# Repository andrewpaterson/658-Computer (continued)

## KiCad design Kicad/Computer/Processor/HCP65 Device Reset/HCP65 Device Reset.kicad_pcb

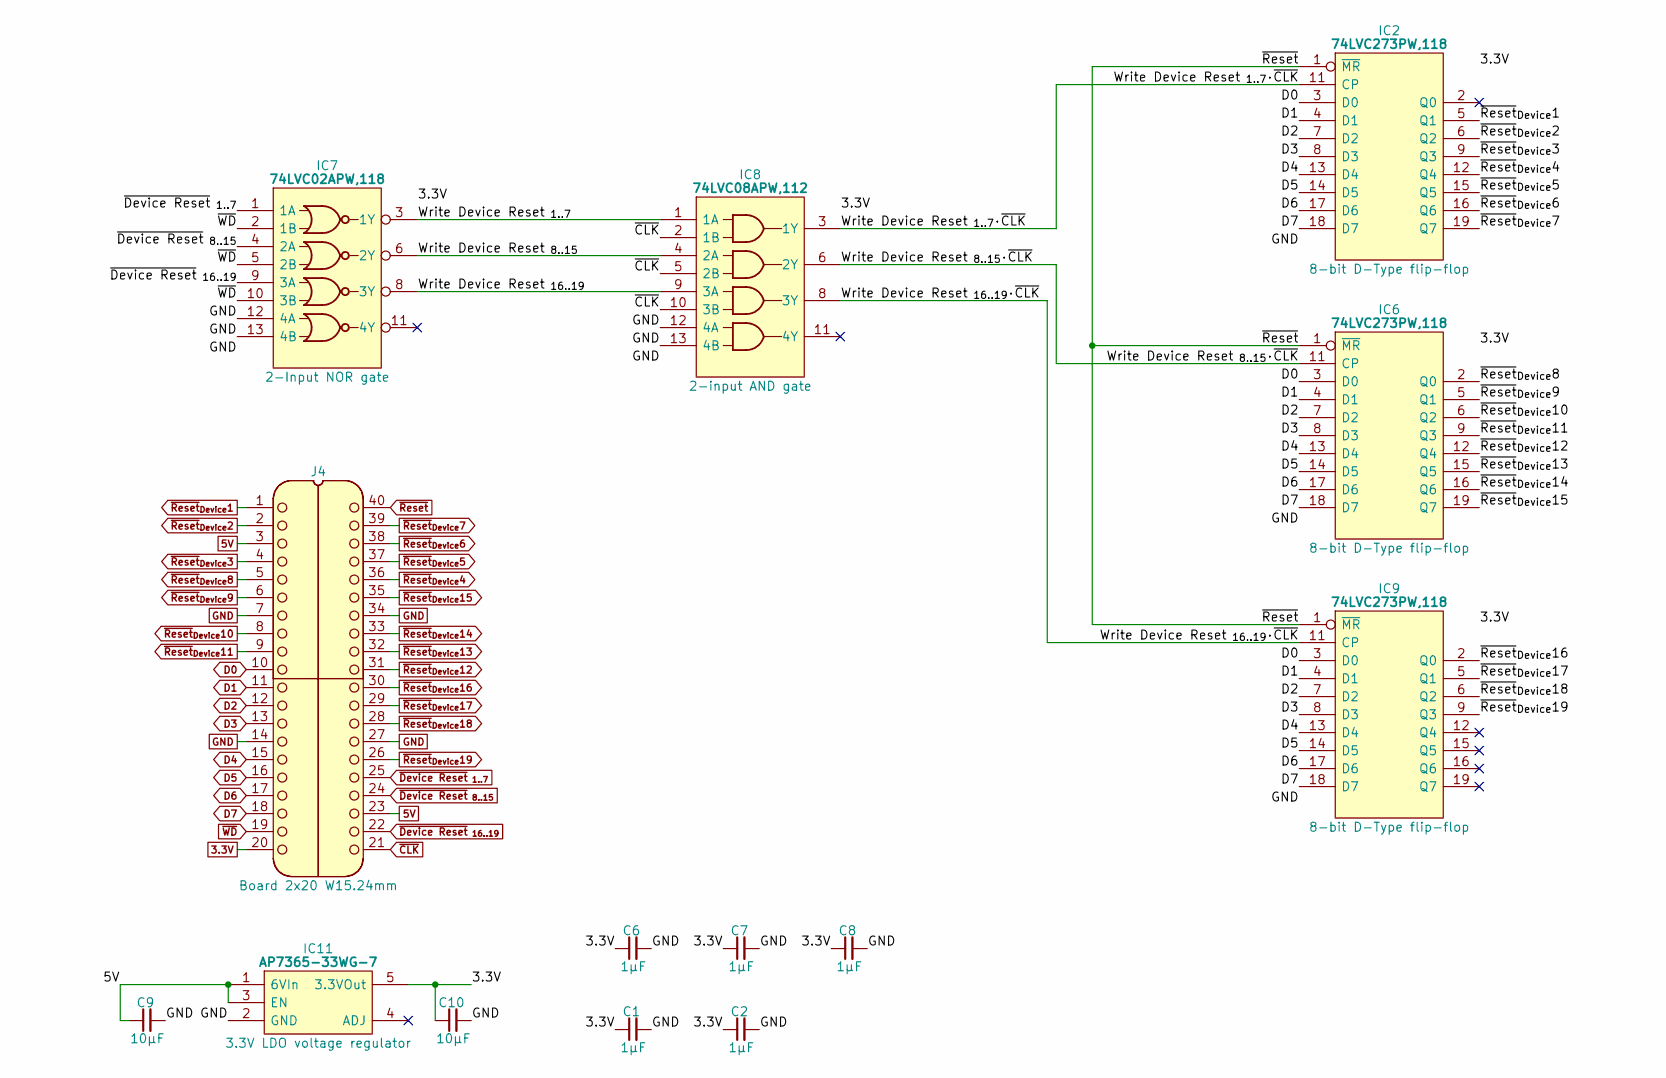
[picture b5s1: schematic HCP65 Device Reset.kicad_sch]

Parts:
C1, C2, C6, C7, C8: 1μF; C_0805
C9, C10: 10μF; C_0805
IC2, IC6, IC9: 74LVC273PW,118; SOP65P640X110-20N; Manufacturer_Part_Number 74LVC273PW,118; Mouser Part Number 771-74LVC273PW-T
IC7: 74LVC02APW,118; SOP65P640X110-14N; Mouser Part Number 771-74LVC02APW-T
IC8: 74LVC08APW,112; SOP65P640X110-14N; Manufacturer_Part_Number 74LVC08APW,112; Mouser Part Number 771-74LVC08APW
IC11: AP7365-33WG-7; SOT95P285X130-5N; Manufacturer_Part_Number AP7365-33WG-7; Mouser Part Number 621-AP7365-33WG-7
J4: Board 2x20 W15.24mm; DIP-40_Board_W15.24mm

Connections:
3.3V: C1.1, C2.1, C6.1, C7.1, C8.1, C10.1, IC2.20 (3V), IC6.20 (3V), IC7.14 (3V), IC8.14 (3V), IC9.20 (3V), IC11.5 (3.3VOut), J4.20
5V: C9.1, IC11.1 (6VIn), IC11.3 (EN), J4.3, J4.23
/Write Device Reset_{ 1..7}: IC7.3 (1Y), IC8.1 (1A)
/Write Device Reset_{ 1..7}·~CLK: IC2.11 (CP), IC8.3 (1Y)
/Write Device Reset_{ 8..15}: IC7.6 (2Y), IC8.4 (2A)
/Write Device Reset_{ 8..15}·~CLK: IC6.11 (CP), IC8.6 (2Y)
/Write Device Reset_{ 16..19}: IC7.8 (3Y), IC8.9 (3A)
/Write Device Reset_{ 16..19}·~CLK: IC8.8 (3Y), IC9.11 (CP)
D0: IC2.3 (D0), IC6.3 (D0), IC9.3 (D0), J4.10
D1: IC2.4 (D1), IC6.4 (D1), IC9.4 (D1), J4.11
D2: IC2.7 (D2), IC6.7 (D2), IC9.7 (D2), J4.12
D3: IC2.8 (D3), IC6.8 (D3), IC9.8 (D3), J4.13
D4: IC2.13 (D4), IC6.13 (D4), IC9.13 (D4), J4.15
D5: IC2.14 (D5), IC6.14 (D5), IC9.14 (D5), J4.16
D6: IC2.17 (D6), IC6.17 (D6), IC9.17 (D6), J4.17
D7: IC2.18 (D7), IC6.18 (D7), IC9.18 (D7), J4.18
GND: C1.2, C2.2, C6.2, C7.2, C8.2, C9.2, C10.2, IC2.10 (GND), IC6.10 (GND), IC7.7 (GND), IC7.12 (4A), IC7.13 (4B), IC8.7 (GND), IC8.12 (4A), IC8.13 (4B), IC9.10 (GND), IC11.2 (GND), J4.7, J4.14, J4.27, J4.34
~CLK: IC8.2 (1B), IC8.5 (2B), IC8.10 (3B), J4.21
~Device Reset_{ 1..7}: IC7.1 (1A), J4.25
~Device Reset_{ 8..15}: IC7.4 (2A), J4.24
~Device Reset_{ 16..19}: IC7.9 (3A), J4.22
~Reset: IC2.1 (~MR), IC6.1 (~MR), IC9.1 (~MR), J4.40
~Reset_{Device}1: IC2.5 (Q1), J4.1
~Reset_{Device}2: IC2.6 (Q2), J4.2
~Reset_{Device}3: IC2.9 (Q3), J4.4
~Reset_{Device}4: IC2.12 (Q4), J4.36
~Reset_{Device}5: IC2.15 (Q5), J4.37
~Reset_{Device}6: IC2.16 (Q6), J4.38
~Reset_{Device}7: IC2.19 (Q7), J4.39
~Reset_{Device}8: IC6.2 (Q0), J4.5
~Reset_{Device}9: IC6.5 (Q1), J4.6
~Reset_{Device}10: IC6.6 (Q2), J4.8
~Reset_{Device}11: IC6.9 (Q3), J4.9
~Reset_{Device}12: IC6.12 (Q4), J4.31
~Reset_{Device}13: IC6.15 (Q5), J4.32
~Reset_{Device}14: IC6.16 (Q6), J4.33
~Reset_{Device}15: IC6.19 (Q7), J4.35
~Reset_{Device}16: IC9.2 (Q0), J4.30
~Reset_{Device}17: IC9.5 (Q1), J4.29
~Reset_{Device}18: IC9.6 (Q2), J4.28
~Reset_{Device}19: IC9.9 (Q3), J4.26
~WD: IC7.2 (1B), IC7.5 (2B), IC7.10 (3B), J4.19

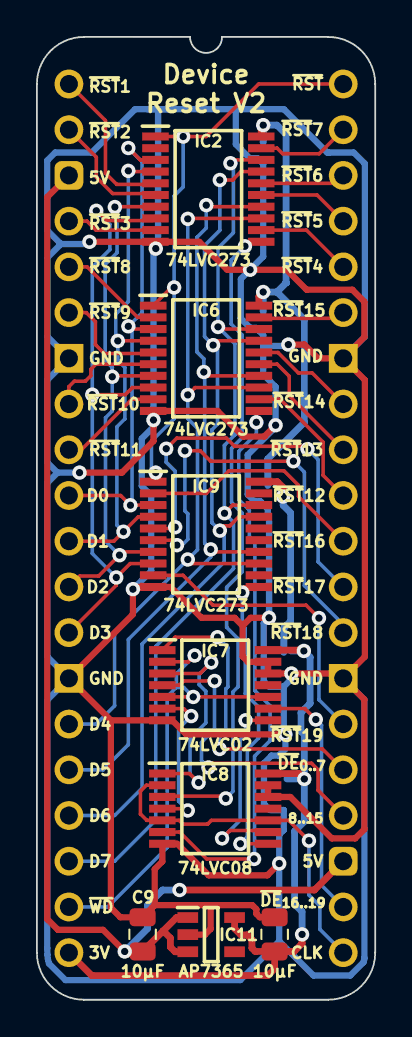
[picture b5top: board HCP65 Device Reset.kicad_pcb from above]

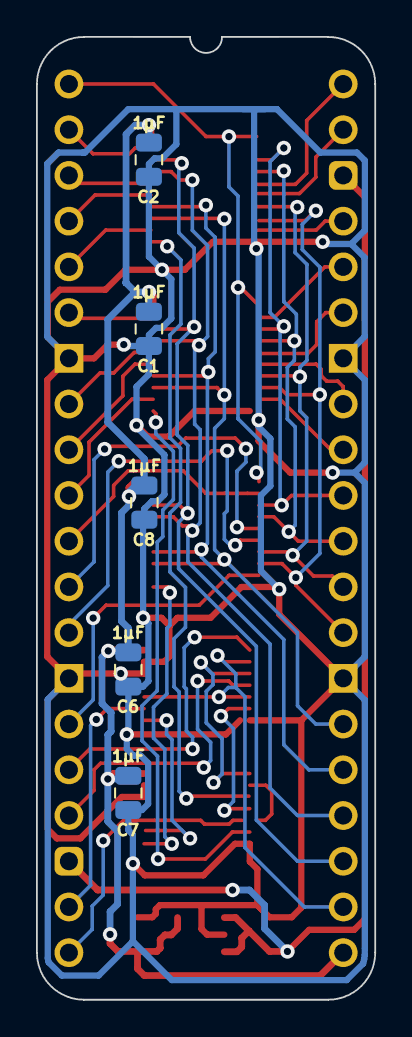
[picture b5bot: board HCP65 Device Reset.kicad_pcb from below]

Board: 2 copper layers, 18.8 x 53.5 mm, 14 parts (5 on the bottom side), 42 nets.

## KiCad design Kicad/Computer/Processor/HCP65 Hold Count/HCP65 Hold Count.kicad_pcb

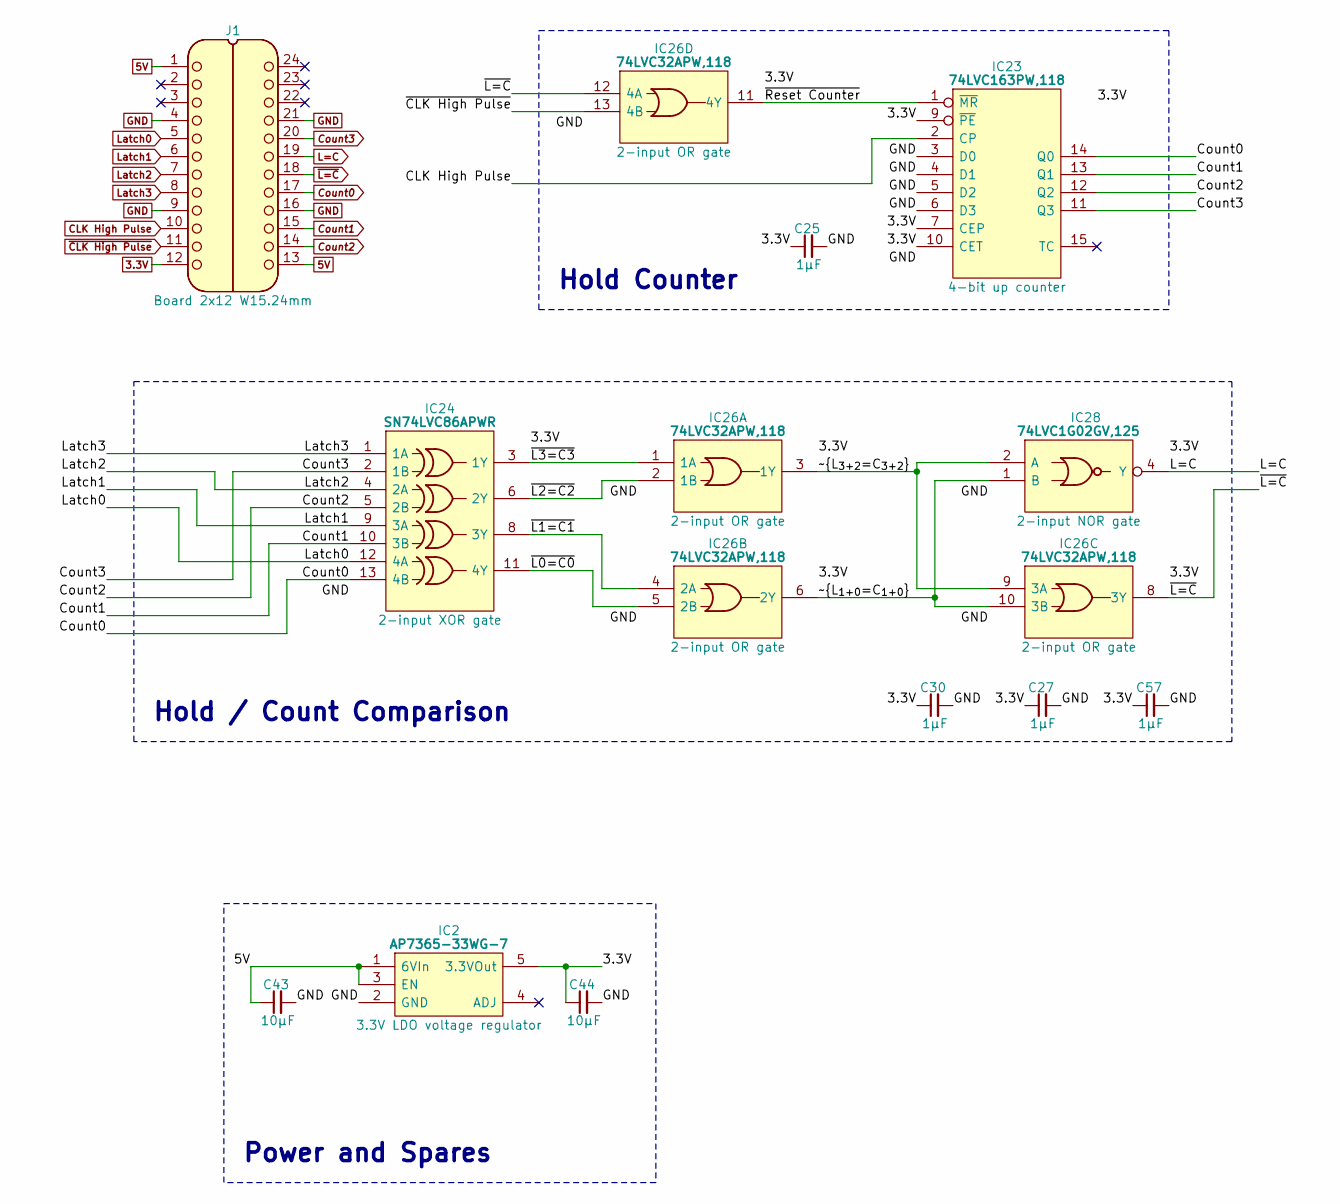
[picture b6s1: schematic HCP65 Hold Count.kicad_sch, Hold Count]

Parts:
C25, C27, C30, C57: 1μF; C_0805
C43, C44: 10μF; C_0805
IC2: AP7365-33WG-7; SOT95P285X130-5N; Manufacturer_Part_Number AP7365-33WG-7; Mouser Part Number 621-AP7365-33WG-7
IC23: 74LVC163PW,118; SOP65P640X110-16N; Mouser Part Number 771-74LVC163PW-T
IC24: SN74LVC86APWR; SOP65P640X120-14N; Manufacturer_Part_Number SN74LVC86APWR; Mouser Part Number 595-SN74LVC86APWR
IC26: 74LVC32APW,118; SOP65P640X110-14N; Manufacturer_Part_Number 74LVC32APW,118; Mouser Part Number 771-74LVC32APW-T
IC28: 74LVC1G02GV,125; SOT95P275X110-5N; Manufacturer_Part_Number 74LVC1G02GV,125; Mouser Part Number 771-LVC1G02GV125
J1: Board 2x12 W15.24mm; DIP-24_Board_W15.24mm

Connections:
3.3V: C25.1, C27.1, C30.1, C44.1, C57.1, IC2.5 (3.3VOut), IC23.7 (CEP), IC23.9 (~PE), IC23.10 (CET), IC23.16 (3V), IC24.14 (3V), IC26.14 (3V), IC28.5 (3V), J1.12
5V: C43.1, IC2.1 (6VIn), IC2.3 (EN), J1.1, J1.13
/~L0=C0: IC24.11 (4Y), IC26.5 (2B)
/~L1=C1: IC24.8 (3Y), IC26.4 (2A)
/~L2=C2: IC24.6 (2Y), IC26.2 (1B)
/~L3=C3: IC24.3 (1Y), IC26.1 (1A)
/~L_{1+0=C_{1+0}}: IC26.6 (2Y), IC26.10 (3B), IC28.1 (B)
/~L_{3+2=C_{3+2}}: IC26.3 (1Y), IC26.9 (3A), IC28.2 (A)
/~Reset Counter: IC23.1 (~MR), IC26.11 (4Y)
CLK High Pulse: IC23.2 (CP), J1.10
Count0: IC23.14 (Q0), IC24.13 (4B), J1.17
Count1: IC23.13 (Q1), IC24.10 (3B), J1.15
Count2: IC23.12 (Q2), IC24.5 (2B), J1.14
Count3: IC23.11 (Q3), IC24.2 (1B), J1.20
GND: C25.2, C27.2, C30.2, C43.2, C44.2, C57.2, IC2.2 (GND), IC23.3 (D0), IC23.4 (D1), IC23.5 (D2), IC23.6 (D3), IC23.8 (GND), IC24.7 (GND), IC26.7 (GND), IC28.3 (GND), J1.4, J1.9, J1.16, J1.21
L=C: IC28.4 (Y), J1.19
Latch0: IC24.12 (4A), J1.5
Latch1: IC24.9 (3A), J1.6
Latch2: IC24.4 (2A), J1.7
Latch3: IC24.1 (1A), J1.8
~CLK High Pulse: IC26.13 (4B), J1.11
~L=C: IC26.8 (3Y), IC26.12 (4A), J1.18

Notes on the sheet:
Power and Spares
Hold Counter
Hold / Count Comparison

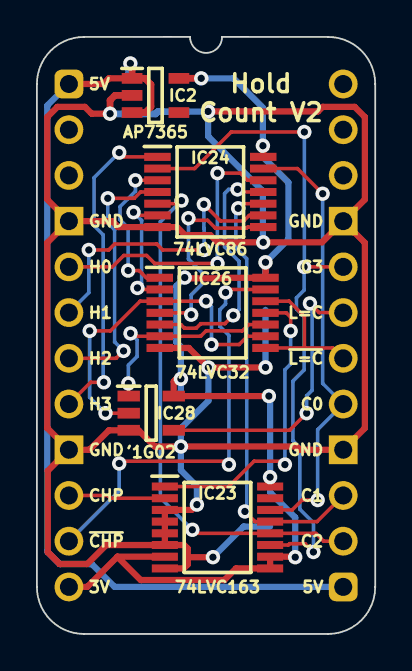
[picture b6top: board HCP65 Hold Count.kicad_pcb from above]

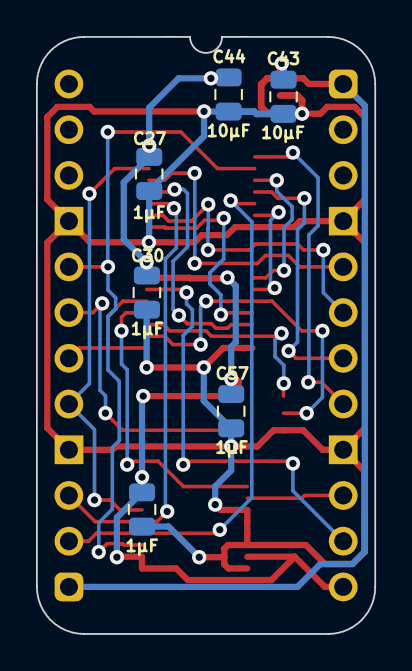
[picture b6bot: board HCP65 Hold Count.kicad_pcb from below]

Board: 2 copper layers, 18.8 x 33.2 mm, 12 parts (6 on the bottom side), 22 nets.

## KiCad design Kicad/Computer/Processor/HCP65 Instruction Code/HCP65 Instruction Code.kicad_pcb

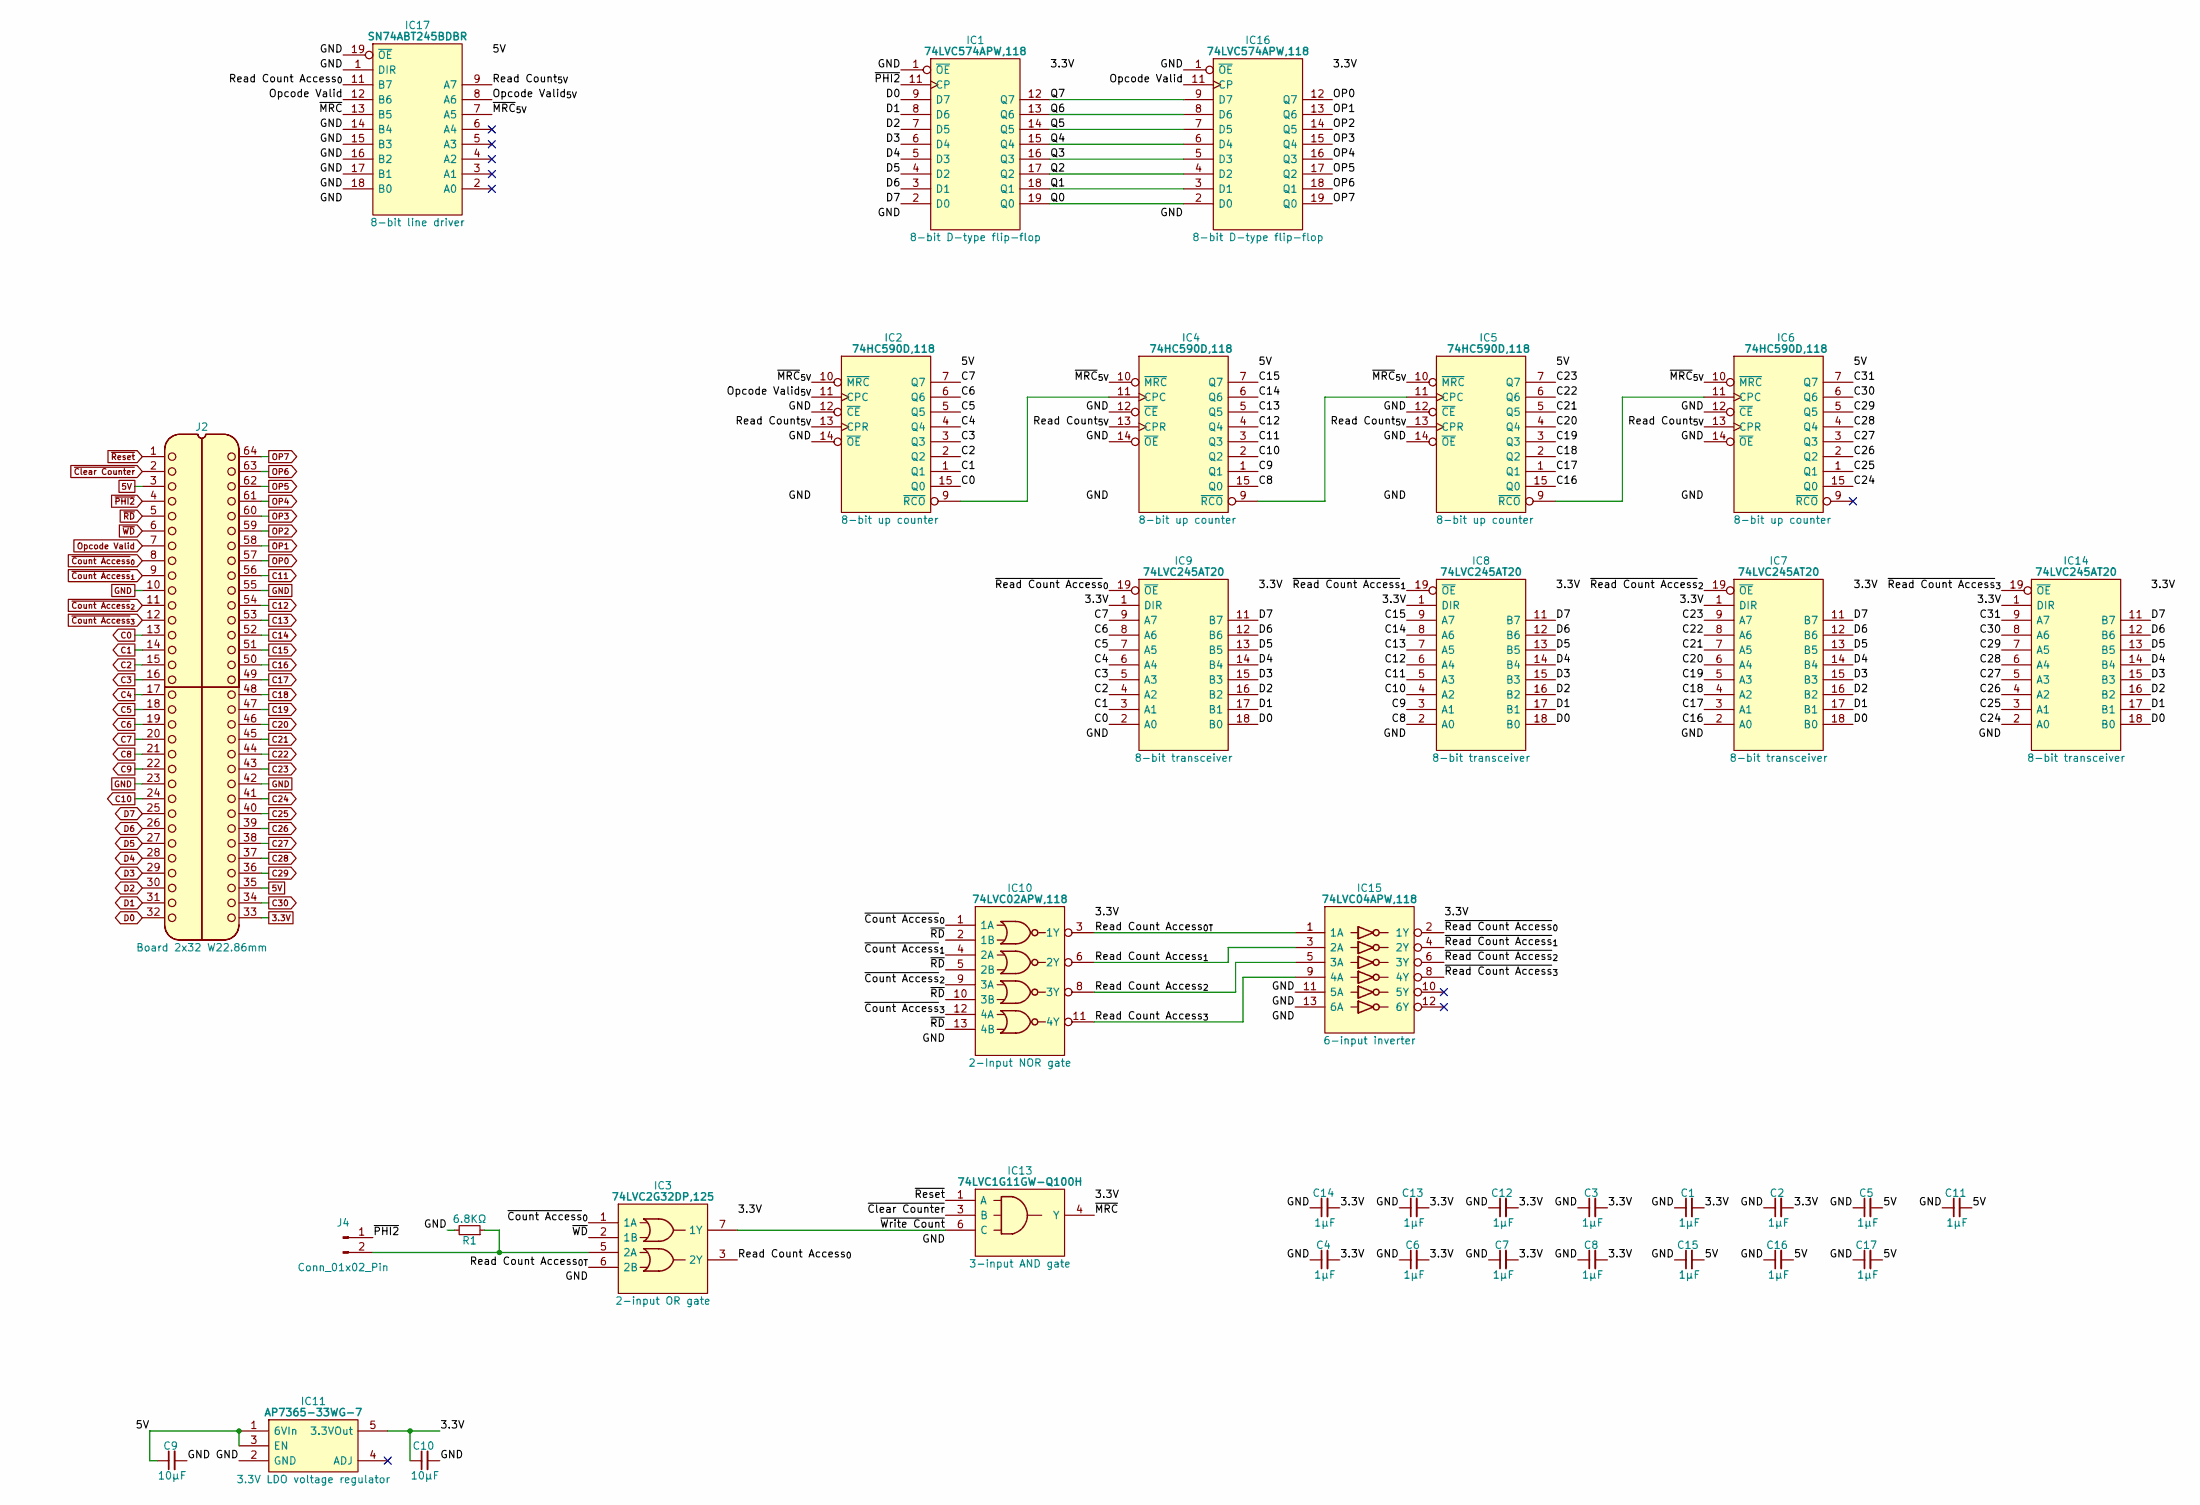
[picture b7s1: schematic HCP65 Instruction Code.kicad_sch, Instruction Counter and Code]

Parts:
C1, C2, C3, C4, C5, C6, C7, C8, C11, C12, C13, C14, C15, C16, C17: 1μF; C_0805
C9, C10: 10μF; C_0805
IC1, IC16: 74LVC574APW,118; SOP65P640X110-20N; Manufacturer_Part_Number 74LVC574APW,118; Mouser Part Number 771-74LVC574APW-T
IC2, IC4, IC5, IC6: 74HC590D,118; SOIC127P600X175-16N; Mouser Part Number 771-HC590D118
IC3: 74LVC2G32DP,125; SOP65P400X110-8N; Manufacturer_Part_Number 74LVC2G32DP,125; Mouser Part Number 771-LVC2G32DP125
IC7, IC8, IC9, IC14: 74LVC245AT20; SOP65P640X120-20N; Manufacturer_Part_Number 74LVC245AT20-13; Mouser Part Number 621-74LVC245AT20-13
IC10: 74LVC02APW,118; SOP65P640X110-14N; Mouser Part Number 771-74LVC02APW-T
IC11: AP7365-33WG-7; SOT95P285X130-5N; Manufacturer_Part_Number AP7365-33WG-7; Mouser Part Number 621-AP7365-33WG-7
IC13: 74LVC1G11GW-Q100H; SOP65P210X110-6N; Manufacturer_Part_Number 74LVC1G11GW-Q100H; Mouser Part Number 771-74LVC1G11GWQ100H
IC15: 74LVC04APW,118; SOP65P640X110-14N; Manufacturer_Part_Number 74LVC04APW,118; Mouser Part Number 771-74LVC04APW-T
IC17: SN74ABT245BDBR; SOP65P780X200-20N; Manufacturer_Part_Number SN74ABT245BDBR; Mouser Part Number 595-SN74ABT245BDBR
J2: Board 2x32 W22.86mm; DIP-64_Board_W22.86mm
J4: Conn_01x02_Pin; PinHeader_1x02_P2.54mm_Vertical
R1: 6.8KΩ; R_0805

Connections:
3.3V: C1.2, C2.2, C3.2, C4.2, C6.2, C7.2, C8.2, C10.1, C12.2, C13.2, C14.2, IC1.20 (3V), IC3.8 (VCC), IC7.1 (DIR), IC7.20 (3V), IC8.1 (DIR), IC8.20 (3V), IC9.1 (DIR), IC9.20 (3V), IC10.14 (3V), IC11.5 (3.3VOut), IC13.5 (3V), IC14.1 (DIR), IC14.20 (3V), IC15.14 (3V), IC16.20 (3V), J2.33
5V: C5.2, C9.1, C11.2, C15.2, C16.2, C17.2, IC2.16 (VCC), IC4.16 (VCC), IC5.16 (VCC), IC6.16 (VCC), IC11.1 (6VIn), IC11.3 (EN), IC17.20 (5V), J2.3, J2.35
/C31: IC6.7 (Q7), IC14.9 (A7)
/Opcode Valid_{5V}: IC2.11 (CPC), IC17.8 (A6)
/Q0: IC1.19 (Q0), IC16.2 (D0)
/Q1: IC1.18 (Q1), IC16.3 (D1)
/Q2: IC1.17 (Q2), IC16.4 (D2)
/Q3: IC1.16 (Q3), IC16.5 (D3)
/Q4: IC1.15 (Q4), IC16.6 (D4)
/Q5: IC1.14 (Q5), IC16.7 (D5)
/Q6: IC1.13 (Q6), IC16.8 (D6)
/Q7: IC1.12 (Q7), IC16.9 (D7)
/Read Count Access_{0T}: IC3.6 (2B), IC10.3 (1Y), IC15.1 (1A)
/Read Count Access_{0}: IC3.3 (2Y), IC17.11 (B7)
/Read Count Access_{1}: IC10.6 (2Y), IC15.3 (2A)
/Read Count Access_{2}: IC10.8 (3Y), IC15.5 (3A)
/Read Count Access_{3}: IC10.11 (4Y), IC15.9 (4A)
/Read Count_{5V}: IC2.13 (CPR), IC4.13 (CPR), IC5.13 (CPR), IC6.13 (CPR), IC17.9 (A7)
/~MRC: IC13.4 (Y), IC17.13 (B5)
/~MRC_{5V}: IC2.10 (~MRC), IC4.10 (~MRC), IC5.10 (~MRC), IC6.10 (~MRC), IC17.7 (A5)
/~Read Count Access_{0}: IC9.19 (~OE), IC15.2 (1Y)
/~Read Count Access_{1}: IC8.19 (~OE), IC15.4 (2Y)
/~Read Count Access_{2}: IC7.19 (~OE), IC15.6 (3Y)
/~Read Count Access_{3}: IC14.19 (~OE), IC15.8 (4Y)
/~Write Count: IC3.7 (1Y), IC13.6 (C)
C0: IC2.15 (Q0), IC9.2 (A0), J2.13
C1: IC2.1 (Q1), IC9.3 (A1), J2.14
C2: IC2.2 (Q2), IC9.4 (A2), J2.15
C3: IC2.3 (Q3), IC9.5 (A3), J2.16
C4: IC2.4 (Q4), IC9.6 (A4), J2.17
C5: IC2.5 (Q5), IC9.7 (A5), J2.18
C6: IC2.6 (Q6), IC9.8 (A6), J2.19
C7: IC2.7 (Q7), IC9.9 (A7), J2.20
C8: IC4.15 (Q0), IC8.2 (A0), J2.21
C9: IC4.1 (Q1), IC8.3 (A1), J2.22
C10: IC4.2 (Q2), IC8.4 (A2), J2.24
C11: IC4.3 (Q3), IC8.5 (A3), J2.56
C12: IC4.4 (Q4), IC8.6 (A4), J2.54
C13: IC4.5 (Q5), IC8.7 (A5), J2.53
C14: IC4.6 (Q6), IC8.8 (A6), J2.52
C15: IC4.7 (Q7), IC8.9 (A7), J2.51
C16: IC5.15 (Q0), IC7.2 (A0), J2.50
C17: IC5.1 (Q1), IC7.3 (A1), J2.49
C18: IC5.2 (Q2), IC7.4 (A2), J2.48
C19: IC5.3 (Q3), IC7.5 (A3), J2.47
C20: IC5.4 (Q4), IC7.6 (A4), J2.46
C21: IC5.5 (Q5), IC7.7 (A5), J2.45
C22: IC5.6 (Q6), IC7.8 (A6), J2.44
C23: IC5.7 (Q7), IC7.9 (A7), J2.43
C24: IC6.15 (Q0), IC14.2 (A0), J2.41
C25: IC6.1 (Q1), IC14.3 (A1), J2.40
C26: IC6.2 (Q2), IC14.4 (A2), J2.39
C27: IC6.3 (Q3), IC14.5 (A3), J2.38
C28: IC6.4 (Q4), IC14.6 (A4), J2.37
C29: IC6.5 (Q5), IC14.7 (A5), J2.36
C30: IC6.6 (Q6), IC14.8 (A6), J2.34
D0: IC1.9 (D7), IC7.18 (B0), IC8.18 (B0), IC9.18 (B0), IC14.18 (B0), J2.32
D1: IC1.8 (D6), IC7.17 (B1), IC8.17 (B1), IC9.17 (B1), IC14.17 (B1), J2.31
D2: IC1.7 (D5), IC7.16 (B2), IC8.16 (B2), IC9.16 (B2), IC14.16 (B2), J2.30
D3: IC1.6 (D4), IC7.15 (B3), IC8.15 (B3), IC9.15 (B3), IC14.15 (B3), J2.29
D4: IC1.5 (D3), IC7.14 (B4), IC8.14 (B4), IC9.14 (B4), IC14.14 (B4), J2.28
D5: IC1.4 (D2), IC7.13 (B5), IC8.13 (B5), IC9.13 (B5), IC14.13 (B5), J2.27
D6: IC1.3 (D1), IC7.12 (B6), IC8.12 (B6), IC9.12 (B6), IC14.12 (B6), J2.26
D7: IC1.2 (D0), IC7.11 (B7), IC8.11 (B7), IC9.11 (B7), IC14.11 (B7), J2.25
GND: C1.1, C2.1, C3.1, C4.1, C5.1, C6.1, C7.1, C8.1, C9.2, C10.2, C11.1, C12.1, C13.1, C14.1, C15.1, C16.1, C17.1, IC1.1 (~OE), IC1.10 (GND), IC2.8 (GND), IC2.12 (~CE), IC2.14 (~OE), IC3.4 (GND), IC4.8 (GND), IC4.12 (~CE), IC4.14 (~OE), IC5.8 (GND), IC5.12 (~CE), IC5.14 (~OE), IC6.8 (GND), IC6.12 (~CE), IC6.14 (~OE), IC7.10 (GND), IC8.10 (GND), IC9.10 (GND), IC10.7 (GND), IC11.2 (GND), IC13.2 (GND), IC14.10 (GND), IC15.7 (GND), IC15.11 (5A), IC15.13 (6A), IC16.1 (~OE), IC16.10 (GND), IC17.1 (DIR), IC17.10 (GND), IC17.14 (B4), IC17.15 (B3), IC17.16 (B2), IC17.17 (B1), IC17.18 (B0), IC17.19 (~OE), J2.10, J2.23, J2.42, J2.55, R1.2
unnamed: IC2.9 (~RCO), IC4.11 (CPC)
unnamed: IC3.5 (2A), J4.2, R1.1
unnamed: IC4.9 (~RCO), IC5.11 (CPC)
unnamed: IC5.9 (~RCO), IC6.11 (CPC)
OP0: IC16.12 (Q7), J2.57
OP1: IC16.13 (Q6), J2.58
OP2: IC16.14 (Q5), J2.59
OP3: IC16.15 (Q4), J2.60
OP4: IC16.16 (Q3), J2.61
OP5: IC16.17 (Q2), J2.62
OP6: IC16.18 (Q1), J2.63
OP7: IC16.19 (Q0), J2.64
Opcode Valid: IC16.11 (CP), IC17.12 (B6), J2.7
~Clear Counter: IC13.3 (B), J2.2
~Count Access_{0}: IC3.1 (1A), IC10.1 (1A), J2.8
~Count Access_{1}: IC10.4 (2A), J2.9
~Count Access_{2}: IC10.9 (3A), J2.11
~Count Access_{3}: IC10.12 (4A), J2.12
~PHI2: IC1.11 (CP), J2.4, J4.1
~RD: IC10.2 (1B), IC10.5 (2B), IC10.10 (3B), IC10.13 (4B), J2.5
~Reset: IC13.1 (A), J2.1
~WD: IC3.2 (1B), J2.6

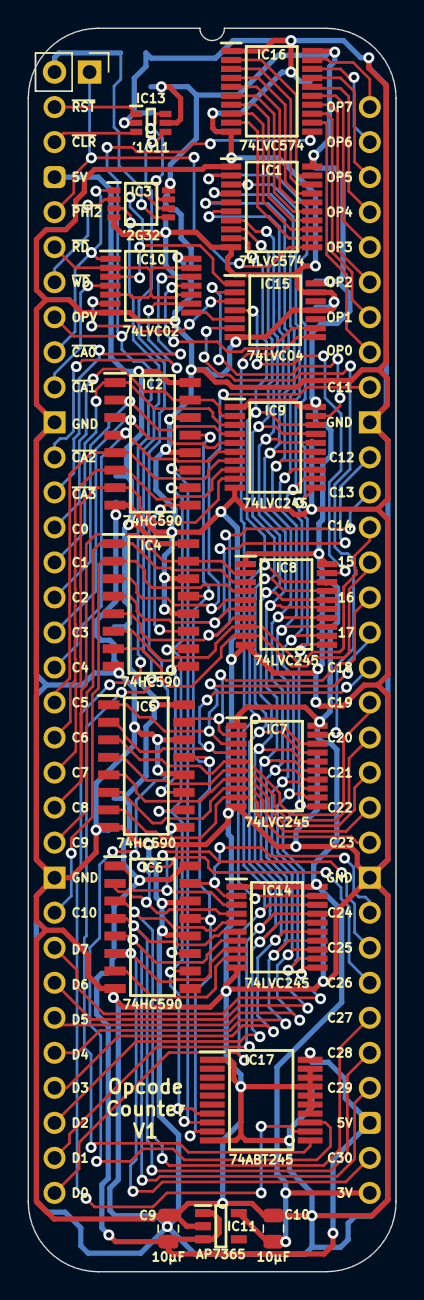
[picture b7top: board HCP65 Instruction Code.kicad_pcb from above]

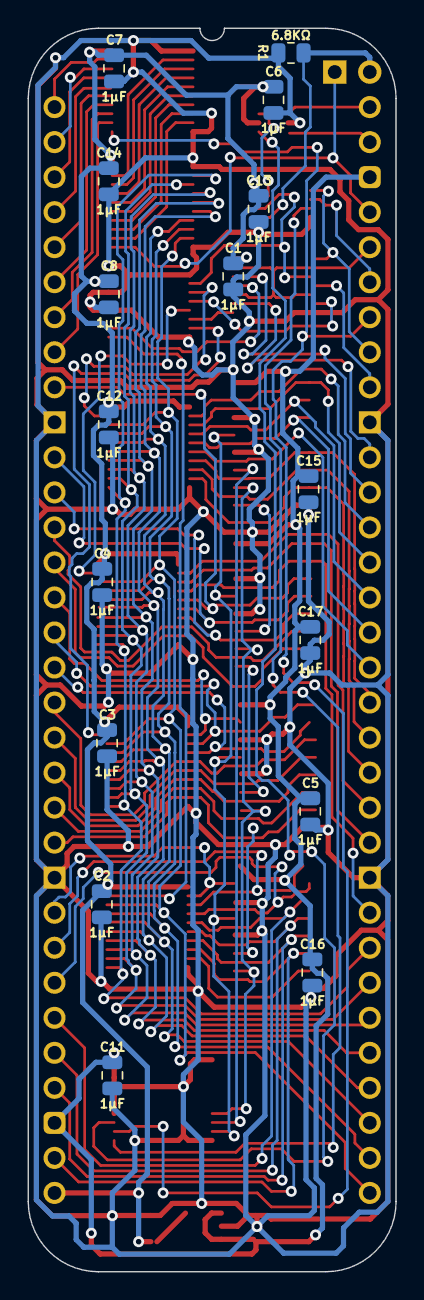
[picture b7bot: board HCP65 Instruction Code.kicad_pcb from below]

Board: 2 copper layers, 26.7 x 90.2 mm, 36 parts (16 on the bottom side), 87 nets.

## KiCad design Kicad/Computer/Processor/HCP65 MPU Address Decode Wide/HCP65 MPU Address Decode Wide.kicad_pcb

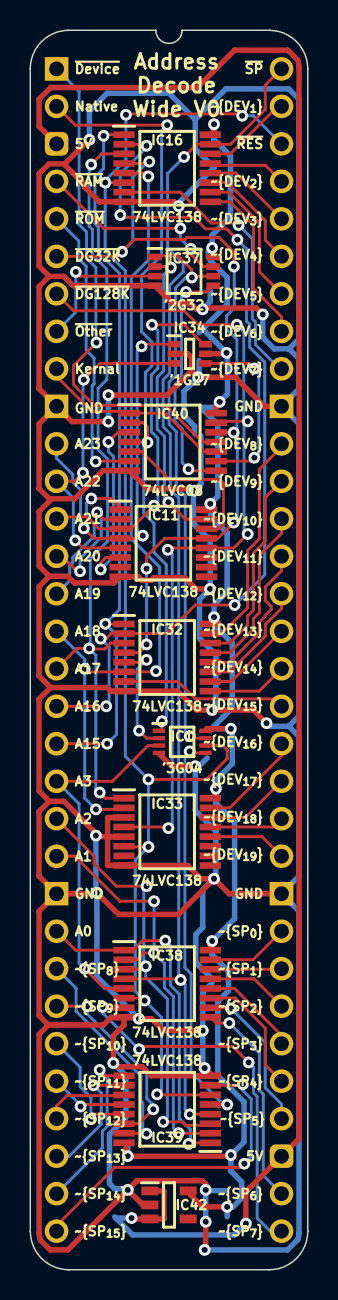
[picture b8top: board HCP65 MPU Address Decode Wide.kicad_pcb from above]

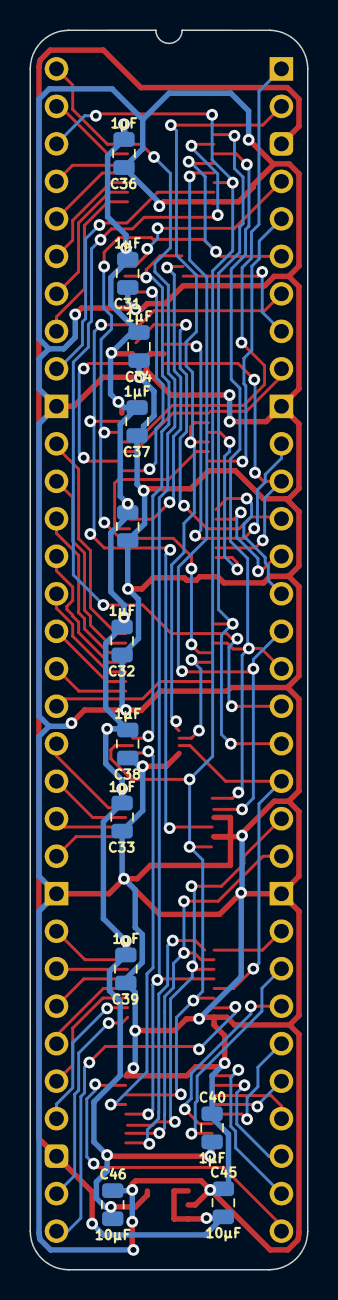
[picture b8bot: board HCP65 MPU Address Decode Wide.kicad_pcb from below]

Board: 2 copper layers, 18.8 x 84.0 mm, 26 parts (14 on the bottom side), 69 nets.

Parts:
C31, C32, C33, C34, C35, C36, C37, C38, C39, C40: 1μF; C_0805
C45, C46: 10μF; C_0805
IC1: SN74LVC3G04DCUR; SOP50P310X90-8N
IC11, IC16, IC32, IC33, IC38, IC39: 74LVC138APW-Q100J; SOP65P640X110-16N
IC34: 74LVC1G27GW,125; SOP65P210X110-6N
IC37: 74LVC2G32DP,125; SOP65P400X110-8N
IC40: 74LVC08APW,112; SOP65P640X110-14N
IC42: AP7365-33WG-7; SOT95P285X130-5N
J1, J3: Pin_Header_01x32; PinHeader_1x32_P2.54mm_Vertical
J2: Conn_02x32_Counter_Clockwise; DIP-64_Board_W15.24mm

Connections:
5V: C45.1, IC42.1 (6VIn), IC42.3 (EN), J2.3, J2.35
/3.3V: C31.1, C32.1, C33.1, C34.1, C35.1, C36.1, C37.1, C38.1, C39.1, C40.1, C46.1, IC1.8 (3V), IC11.16 (3V), IC16.16 (3V), IC32.16 (3V), IC33.16 (3V), IC34.5 (3V), IC37.8 (VCC), IC38.16 (3V), IC39.16 (3V), IC40.14 (3V), IC42.5 (3.3VOut)
/Kernal Mode·Native Latch: IC11.6 (E3), IC40.3 (1Y)
/Reset: IC1.2 (3Y), IC32.5 (~E2)
/~A3: IC1.5 (2Y), IC39.5 (~E2)
/~A21+A22+A23: IC34.4 (Y), IC40.9 (3A)
/~Native Latch: IC1.7 (1Y), IC37.1 (1A), IC37.6 (2B)
/~RAM: IC11.15 (~Y0), IC37.2 (1B)
/~ROM: IC11.14 (~Y1), IC40.5 (2B)
A0: IC38.1 (A0), IC39.1 (A0), J2.24
A1: IC38.2 (A1), IC39.2 (A1), J2.22
A2: IC38.3 (A2), IC39.3 (A2), J2.21
A3: IC1.3 (2A), IC38.5 (~E2), J2.20
A15: IC16.1 (A0), IC32.1 (A0), J2.19
A16: IC16.2 (A1), IC32.2 (A1), J2.18
A17: IC16.3 (A2), IC32.3 (A2), IC33.1 (A0), J2.17
A18: IC16.5 (~E2), IC32.6 (E3), IC33.2 (A1), J2.16
A19: IC11.1 (A0), J2.15
A20: IC11.2 (A1), J2.14
A21: IC11.3 (A2), IC34.6 (C), J2.13
A22: IC11.5 (~E2), IC34.3 (B), J2.12
A23: IC11.4 (~E1), IC34.1 (A), J2.11
GND: C31.2, C32.2, C33.2, C34.2, C35.2, C36.2, C37.2, C38.2, C39.2, C40.2, C45.2, C46.2, IC1.4 (GND), IC11.8 (GND), IC16.8 (GND), IC32.8 (GND), IC33.3 (A2), IC33.5 (~E2), IC33.8 (GND), IC34.2 (GND), IC37.4 (GND), IC38.8 (GND), IC39.8 (GND), IC40.7 (GND), IC42.2 (GND), J2.10, J2.23, J2.42, J2.55
Kernal Mode: IC40.1 (1A), IC40.10 (3B), J2.9
Native Latch: IC1.1 (1A), IC40.2 (1B), IC40.4 (2A), J2.2
unnamed: IC37.5 (2A), IC40.8 (3Y)
~Device Group 32K: IC11.13 (~Y2), IC16.4 (~E1), IC32.4 (~E1), IC40.12 (4A), J2.6
~Device Group 128K: IC11.12 (~Y3), IC33.4 (~E1), IC40.13 (4B), J2.7
~Device _{CS1}: IC16.14 (~Y1), J2.63
~Device _{CS2}: IC16.13 (~Y2), J2.61
~Device _{CS3}: IC16.12 (~Y3), J2.60
~Device _{CS4}: IC16.11 (~Y4), J2.59
~Device _{CS5}: IC16.10 (~Y5), J2.58
~Device _{CS6}: IC16.9 (~Y6), J2.57
~Device _{CS7}: IC16.7 (~Y7), J2.56
~Device _{CS8}: IC32.15 (~Y0), J2.54
~Device _{CS9}: IC32.14 (~Y1), J2.53
~Device _{CS10}: IC32.13 (~Y2), J2.52
~Device _{CS11}: IC32.12 (~Y3), J2.51
~Device _{CS12}: IC32.11 (~Y4), J2.50
~Device _{CS13}: IC32.10 (~Y5), J2.49
~Device _{CS14}: IC32.9 (~Y6), J2.48
~Device _{CS15}: IC32.7 (~Y7), J2.47
~Device _{CS16}: IC33.15 (~Y0), J2.46
~Device _{CS17}: IC33.14 (~Y1), J2.45
~Device _{CS18}: IC33.13 (~Y2), J2.44
~Device _{CS19}: IC33.12 (~Y3), J2.43
~Device: IC40.11 (4Y), J2.1
~OTHER: IC37.3 (2Y), J2.8
~RAM_{CS}: IC37.7 (1Y), J2.4
~ROM_{CS}: IC40.6 (2Y), J2.5
~Reset: IC1.6 (3A), IC16.6 (E3), IC33.6 (E3), IC38.6 (E3), IC39.6 (E3), J2.62
~SPECIAL: IC16.15 (~Y0), IC38.4 (~E1), IC39.4 (~E1), J2.64
~Special _{CS0}: IC38.15 (~Y0), J2.41
~Special _{CS1}: IC38.14 (~Y1), J2.40
~Special _{CS2}: IC38.13 (~Y2), J2.39
~Special _{CS3}: IC38.12 (~Y3), J2.38
~Special _{CS4}: IC38.11 (~Y4), J2.37
~Special _{CS5}: IC38.10 (~Y5), J2.36
~Special _{CS6}: IC38.9 (~Y6), J2.34
~Special _{CS7}: IC38.7 (~Y7), J2.33
~Special _{CS8}: IC39.15 (~Y0), J2.25
~Special _{CS9}: IC39.14 (~Y1), J2.26
~Special _{CS10}: IC39.13 (~Y2), J2.27
~Special _{CS11}: IC39.12 (~Y3), J2.28
~Special _{CS12}: IC39.11 (~Y4), J2.29
~Special _{CS13}: IC39.10 (~Y5), J2.30
~Special _{CS14}: IC39.9 (~Y6), J2.31
~Special _{CS15}: IC39.7 (~Y7), J2.32
